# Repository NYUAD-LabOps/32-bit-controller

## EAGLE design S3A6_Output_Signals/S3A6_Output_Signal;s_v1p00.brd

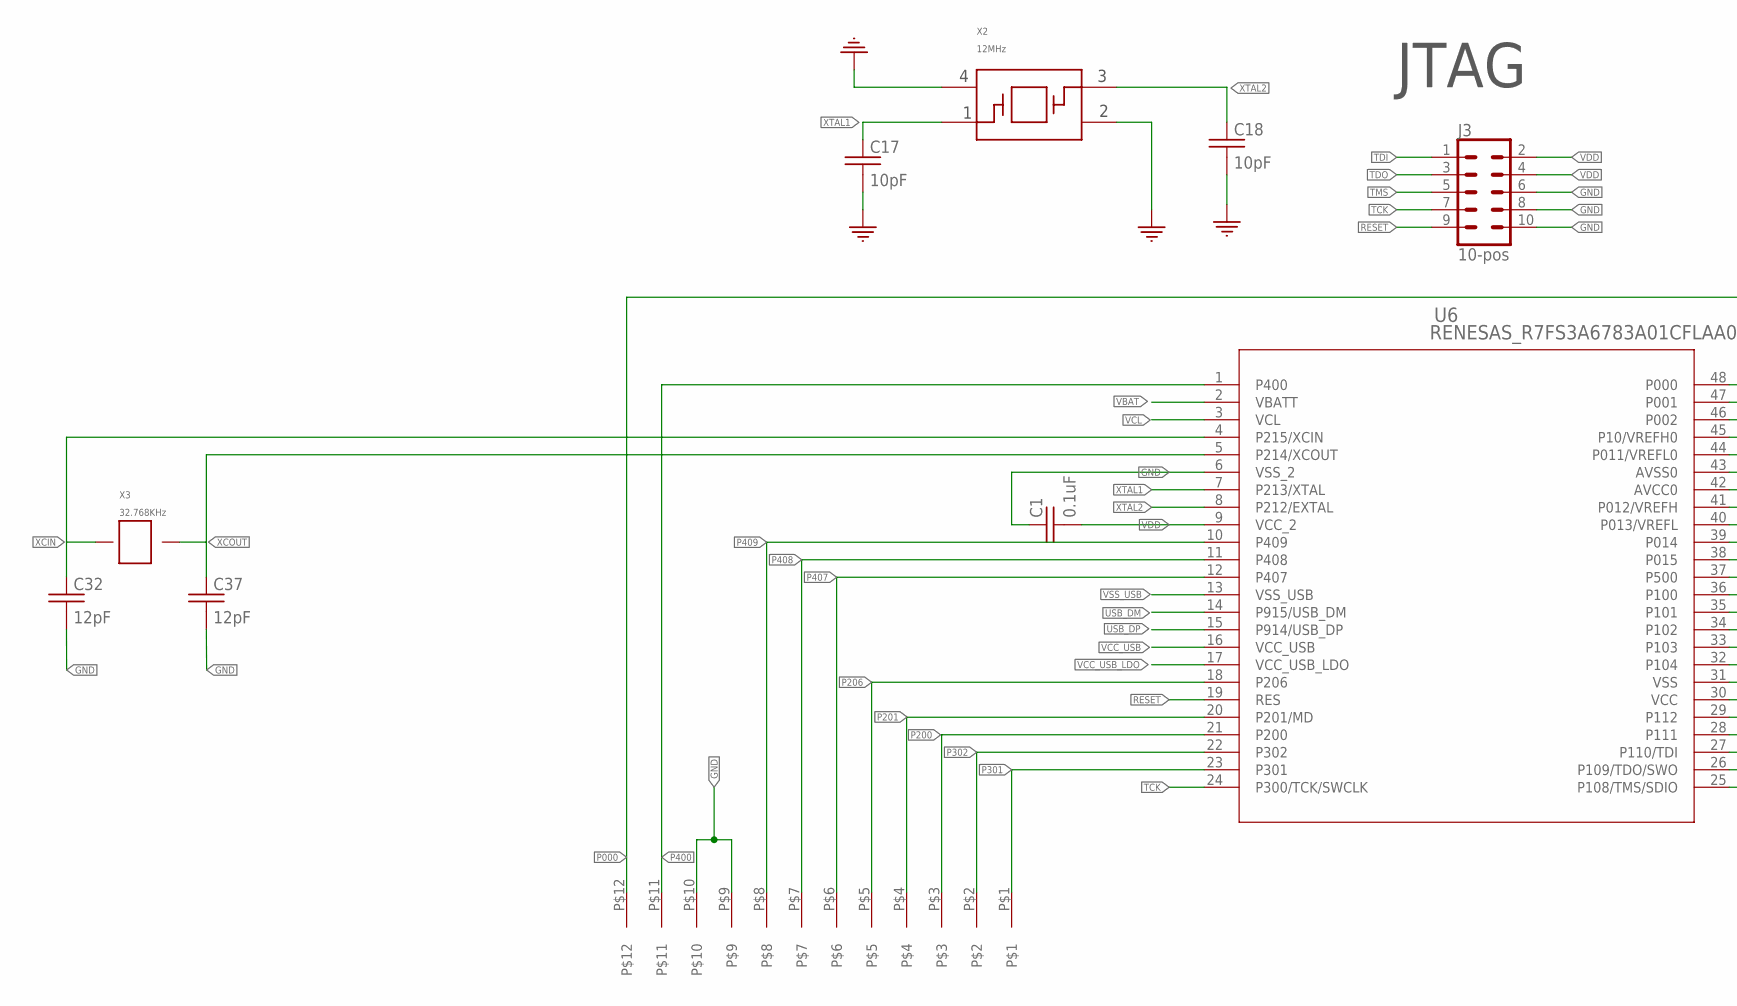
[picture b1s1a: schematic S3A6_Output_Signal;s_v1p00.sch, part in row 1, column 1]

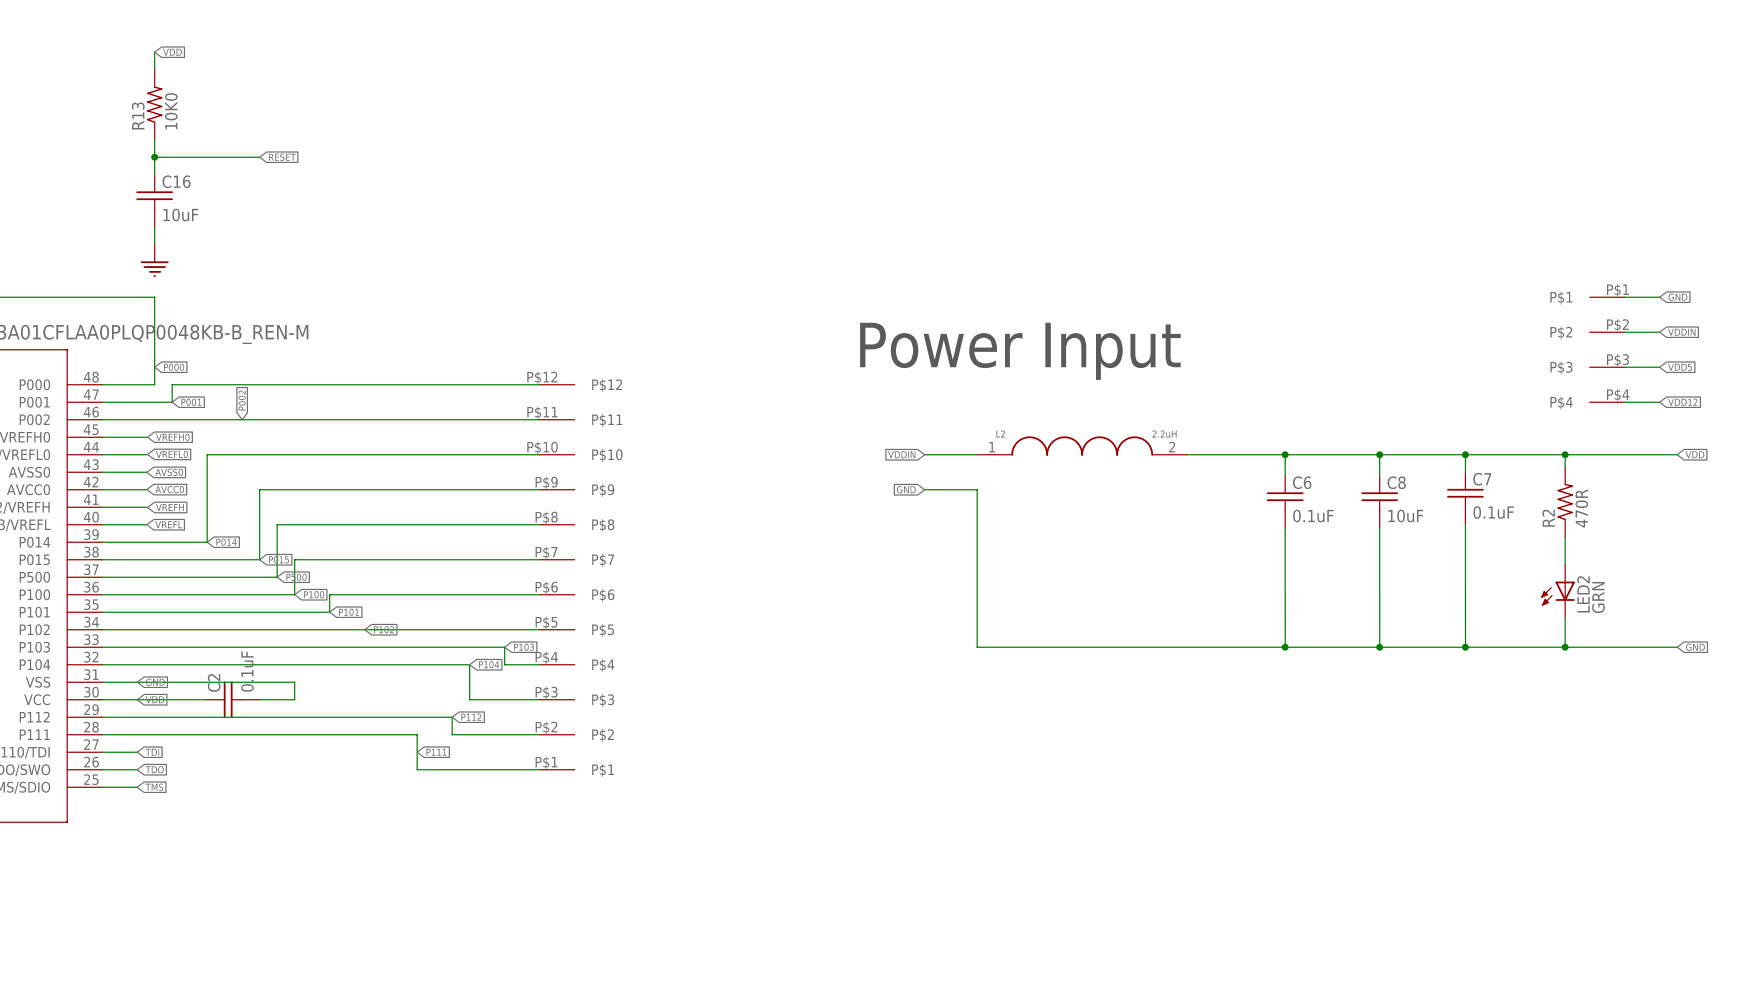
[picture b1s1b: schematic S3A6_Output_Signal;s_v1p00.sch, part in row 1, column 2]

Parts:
C1, C2, C6, C7: 0.1uF; 0402
C8, C16: 10uF; 0402
C17, C18: 10pF; 0402
C32, C37: 12pF; 0402
J3: 10-pos; 2X5
L2: 2.2uH; 1008_(2520_METRIC)
LED2: LED_0805_GREEN
PWR1: 4-pos; 1X4_3.81MM_PITCH
R2: 470R; 0402
R13: 10K0; 0402
U6: RENESAS_R7FS3A6783A01CFLAA0PLQP0048KB-B_REN-M; PLQP0048KB-B_REN-M
U$1, U$2: 1_X_12_HEADER_GENERIC_.1INCH; HEADER_1_X_12_.1_INCH
X2: 12MHz; SMD_3225
X3: 32.768KHz; SMD_X_2_PADS

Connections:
AVCC0: U6.42 (AVCC0)
AVSS0: U6.43 (AVSS0)
GND: C1.P$1 (1), C2.P$2 (2), C6.P$2 (2), C7.P$2 (2), C8.P$2 (2), C16.P$2 (2), C17.P$2 (2), C18.P$2 (2), C32.P$2 (2), C37.P$2 (2), J3.6, J3.8, J3.10, LED2.C, PWR1.P$1, U6.6 (VSS_2), U6.31 (VSS), U$1.P$9, U$1.P$10, X2.2, X2.4
unnamed: LED2.A, R2.P$1 (1)
P000: U6.48 (P000), U$1.P$12
P001: U6.47 (P001), U$2.P$12
P002: U6.46 (P002), U$2.P$11
P014: U6.39 (P014), U$2.P$10
P015: U6.38 (P015), U$2.P$9
P100: U6.36 (P100), U$2.P$7
P101: U6.35 (P101), U$2.P$6
P102: U6.34 (P102), U$2.P$5
P103: U6.33 (P103), U$2.P$4
P104: U6.32 (P104), U$2.P$3
P111: U6.28 (P111), U$2.P$1
P112: U6.29 (P112), U$2.P$2
P200: U6.21 (P200), U$1.P$3
P201: U6.20 (P201/MD), U$1.P$4
P206: U6.18 (P206), U$1.P$5
P301: U6.23 (P301), U$1.P$1
P302: U6.22 (P302), U$1.P$2
P400: U6.1 (P400), U$1.P$11
P407: U6.12 (P407), U$1.P$6
P408: U6.11 (P408), U$1.P$7
P409: U6.10 (P409), U$1.P$8
P500: U6.37 (P500), U$2.P$8
RESET: C16.P$1 (1), J3.9, R13.P$1 (1), U6.19 (RES)
TCK: J3.7, U6.24 (P300/TCK/SWCLK)
TDI: J3.1, U6.27 (P110/TDI)
TDO: J3.3, U6.26 (P109/TDO/SWO)
TMS: J3.5, U6.25 (P108/TMS/SDIO)
USB_DM: U6.14 (P915/USB_DM)
USB_DP: U6.15 (P914/USB_DP)
VBAT: U6.2 (VBATT)
VCC_USB: U6.16 (VCC_USB)
VCC_USB_LDO: U6.17 (VCC_USB_LDO)
VCL: U6.3 (VCL)
VDD: C1.P$2 (2), C2.P$1 (1), C6.P$1 (1), C7.P$1 (1), C8.P$1 (1), J3.2, J3.4, L2.2, R2.P$2 (2), R13.P$2 (2), U6.9 (VCC_2), U6.30 (VCC)
VDD5: PWR1.P$3
VDD12: PWR1.P$4
VDDIN: L2.1, PWR1.P$2
VREFH: U6.41 (P012/VREFH)
VREFH0: U6.45 (P10/VREFH0)
VREFL: U6.40 (P013/VREFL)
VREFL0: U6.44 (P011/VREFL0)
VSS_USB: U6.13 (VSS_USB)
XCIN: C32.P$1 (1), U6.4 (P215/XCIN), X3.P$1
XCOUT: C37.P$1 (1), U6.5 (P214/XCOUT), X3.P$2
XTAL1: C17.P$1 (1), U6.7 (P213/XTAL), X2.1
XTAL2: C18.P$1 (1), U6.8 (P212/EXTAL), X2.3

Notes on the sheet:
JTAG
Power Input

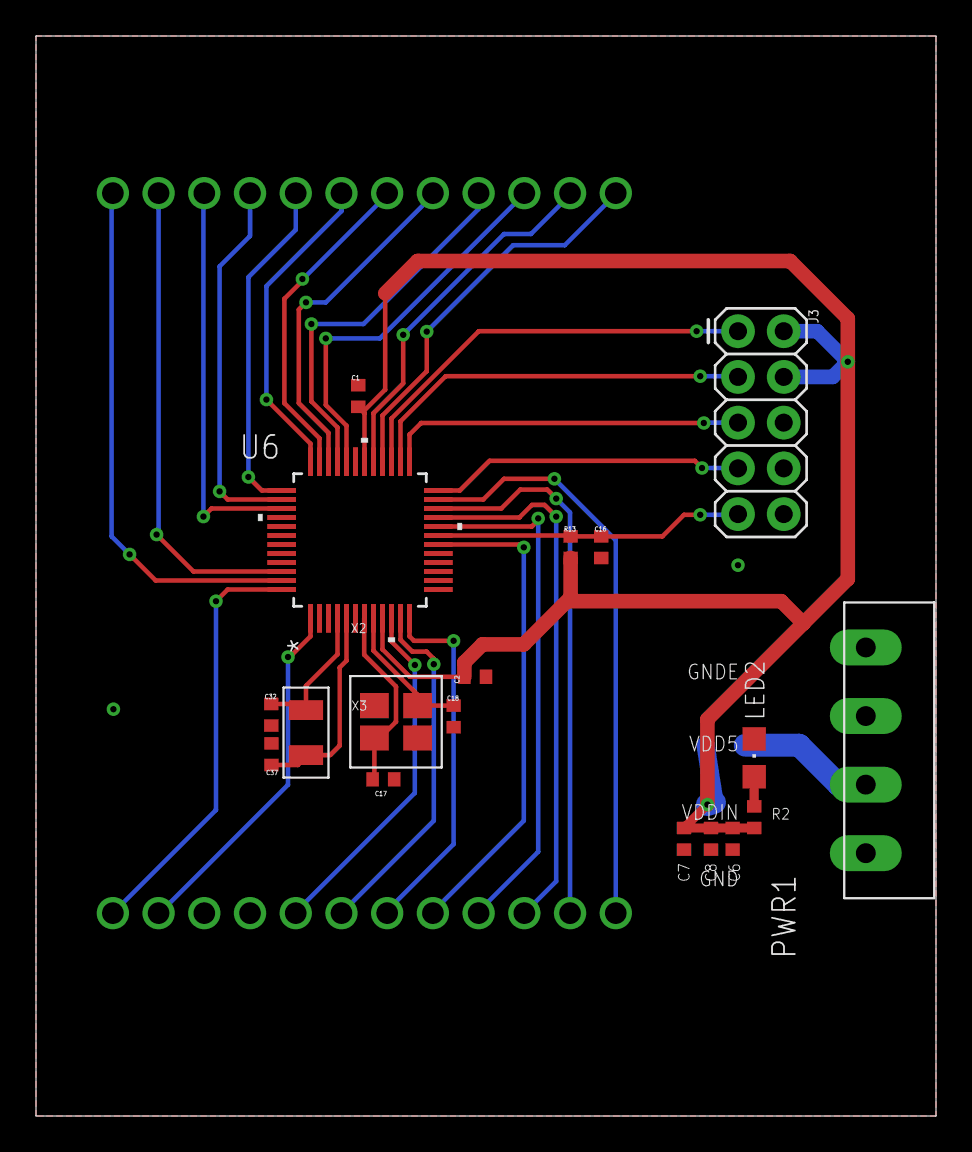
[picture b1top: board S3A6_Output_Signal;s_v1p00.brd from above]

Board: 2 copper layers, 50.0 x 60.0 mm, 21 parts (1 on the bottom side), 35 nets.

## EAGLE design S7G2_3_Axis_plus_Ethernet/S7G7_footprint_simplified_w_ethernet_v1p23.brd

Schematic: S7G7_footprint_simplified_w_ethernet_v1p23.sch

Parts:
C1, C8, C10, C11, C13, C14, C30, C31, C33, C34, C36, C37, C38, C39, C40, C44, C46, C49, C54, C55, C56, C58, C59, C60, C61: 0.1uF; 0402
C2, C16, C32: 1uF; 0402
C5, C35, C57: 10uF; 0402
C15: 100uF; C1210
C41, C42: 24pF; 0402
C43, C48: 22uF; 0603
C45: 2.2uF; 0402
C47: 100pF; 0402
C50, C51: 12pF; 0402
C52, C53: 18pF; 0402
FB2/2: FB_0805_120_OHM; 0805
J1, J11: CONN_05X2PTH; 2X5
J2: USB_MICRO-B
J3: USB_A; USB_A_SMT
J4: RJ45_WITH_ELEC; RJ45_TH_ELEC
J5, J6, J13, J14, J15: 3.81MM_1_X_4_RT_ANGLE_PLUG_HEADER; 1X4_3.81MM_PITCH
J7, J8, J12: CONN_05X2NO_SILK; 2X5_NOSILK
J9: SD_CARD_1140084168; AMPHENOL_1140084168
J10: HEADER_2_X_20_GENERIC; HEADER_2_X_20_.1_INCH
J16: CONN_05X2SHD_SMD; 2X5-SHROUDED_SMD
L3: 2.2uH; 1008_(2520_METRIC)
LED3: LED_0805_GREEN
R1, R12, R16, R17, R18, R26, R27: 10K0; 0402
R2, R3, R8, R9, R10, R11, R14, R20, R21: 1K; 0402
R4: 15K0; 0402
R5, R6: 27R0; 0402
R7: 30K0; 0402
R13, R23, R24: 470R0; 0402
R19: 2.2K; 0402
R25: 6k49; 0402
R28, R29: 1K50; 0402
R30, R31, R32, R33: 33R0; 0402
RXS2, RXS3, RXS4, RXS8: 1K; 0402
RYS3, RYS4, RYS5, RYS6, RYS7, RYS8, RYS15, RYS16: 1K; 0402
RZS2, RZS3, RZS4, RZS8: 1K; 0402
U2: AP2141DWG-5; SOT-23-5
U3: KSZ8081RNACAQFN-24-M; QFN-24-M
U4: S7G2LQFP176; LQFP176_24X24
U7, U8, U9, U10, U12, U13, U14, U15, U16, U17, U18, U19, U32, U33, U34, U35: BC846BW; SOT323
U$1, U$5, U$6, U$8, U$10, U$12, U$13, U$14, U$15, U$16, U$17, U$18, U$32, U$33, U$34, U$35: 1K; 0402
U$3: XTAL_25_MHZ; SMD_3225
U$4: 10uF; 0402
X3: 32.768KHZ; SMD_X_2_PADS
X4: 24MHZ; SMD_3225

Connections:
C58: C39.P$1 (1), J4.4 (CT1)
C60: C40.P$1 (1), J4.5 (CT2)
CRS_DV: R33.P$2 (2), U3.15 (CRS_DV/PHYAD[1:0])
D+: J2.P$3 (D+), R6.P$2 (2)
D-: J2.P$2 (D-), R5.P$2 (2)
ETH: U3.16 (REF_CLK), U4.9 (P7_1)
ETH_CRS_DV: R33.P$1 (1), U4.13 (P7_5)
ETH_IRQ14: R26.P$1 (1), U3.18 (INTRP), U4.159 (P0_10/AN103)
ETH_MDC: R28.P$1 (1), U3.11 (MDC), U4.4 (P4_3)
ETH_MDIO: R29.P$1 (1), U3.10 (MDIO), U4.5 (P4_4)
ETH_RESET: R27.P$1 (1), U3.24 (!RST), U4.172 (P8_6), U$4.P$1 (1)
ETH_RXD0: R31.P$1 (1), U4.10 (P7_2)
ETH_RXD1: R30.P$1 (1), U4.11 (P7_3)
ETH_RX_ER: R32.P$1 (1), U4.12 (P7_4)
ETH_TXD0: U3.20 (TXD0), U4.8 (P7_0)
ETH_TXD1: U3.21 (TXD1), U4.7 (P4_6)
ETH_TXD_EN: U3.19 (TXEN), U4.6 (P4_5)
F0_OUT: J5.P$1, J6.P$1, J13.P$1, J14.P$1, U8.3 (C(3)), U13.3 (C(3)), U17.3 (C(3)), U33.3 (C(3))
F1_OUT: J5.P$2, J6.P$2, J13.P$2, J14.P$2, U9.3 (C(3)), U14.3 (C(3)), U18.3 (C(3)), U34.3 (C(3))
F2_OUT: J5.P$3, J6.P$3, J13.P$3, J14.P$3, U7.3 (C(3)), U12.3 (C(3)), U16.3 (C(3)), U32.3 (C(3))
F3_OUT: J5.P$4, J6.P$4, J13.P$4, J14.P$4, U10.3 (C(3)), U15.3 (C(3)), U19.3 (C(3)), U35.3 (C(3))
GND: C1.P$1 (1), C2.P$1 (1), C5.P$2 (2), C8.P$2 (2), C10.P$1 (1), C11.P$2 (2), C13.P$1 (1), C14.P$1 (1), C15.2, C16.P$2 (2), C30.P$1 (1), C31.P$2 (2), C32.P$2 (2), C33.P$2 (2), C34.P$2 (2), C35.P$2 (2), C36.P$1 (1), C37.P$1 (1), C38.P$2 (2), C39.P$2 (2), C40.P$2 (2), C41.P$2 (2), C42.P$2 (2), C43.2, C44.P$2 (2), C45.P$2 (2), C46.P$2 (2), C47.P$2 (2), C48.2, C49.P$2 (2), C50.P$2 (2), C51.P$2 (2), C52.P$2 (2), C53.P$2 (2), C54.P$1 (1), C55.P$1 (1), C56.P$1 (1), C57.P$2 (2), C58.P$2 (2), C59.P$2 (2), C60.P$2 (2), C61.P$1 (1), J1.1, J1.2, J2.P$5 (GND), J3.GND, J4.8, J4.10 (GLO), J9.6 (SUPPLY_VOLTAGE_GROUND), J11.6, J11.8, J11.10, J16.2, J16.4, J16.6, J16.8, J16.10, LED3.C, R7.P$1 (1), R16.P$1 (1), R17.P$1 (1), R19.P$1 (1), R25.P$1 (1), U2.2 (GND), U3.22 (GND), U3.25, U4.22 (VSS1), U4.28 (AVSS_USBHS), U4.29 (PVSS_USBHS), U4.30 (VSS2_USBHS), U4.33 (VSS1_USBHS), U4.35 (VSSIO), U4.45 (VSS_USB), U4.60 (VSS(IO)2), U4.63 (VSS(IO/DCDC)), U4.66 (VCC_DCDC(IO/DCDC)), U4.83 (VSS(IO)3), U4.98 (VSS(IO)4), U4.111 (VSS(IO)5), U4.124 (VSS(IO)6), U4.139 (VSS(IO)7), U4.150 (VSS(IO)8), U4.153 (VREFL), U4.156 (AVSS0), U4.157 (VREFL0), U4.170 (VSS(IO)9), U7.2 (E(1)), U8.2 (E(1)), U9.2 (E(1)), U10.2 (E(1)), U12.2 (E(1)), U13.2 (E(1)), U14.2 (E(1)), U15.2 (E(1)), U16.2 (E(1)), U17.2 (E(1)), U18.2 (E(1)), U19.2 (E(1)), U32.2 (E(1)), U33.2 (E(1)), U34.2 (E(1)), U35.2 (E(1)), U$1.P$2 (2), U$3.2, U$3.4, U$4.P$2 (2), U$5.P$2 (2), U$6.P$2 (2), U$8.P$2 (2), U$10.P$2 (2), U$12.P$2 (2), U$13.P$2 (2), U$14.P$2 (2), U$15.P$2 (2), U$16.P$2 (2), U$17.P$2 (2), U$18.P$2 (2), U$32.P$2 (2), U$33.P$2 (2), U$34.P$2 (2), U$35.P$2 (2), X4.2, X4.4
GNDE: J1.9, J1.10, J2.P$6 (SHIELD1), J2.P$7 (SHIELD2), J2.P$8 (SHIELD3), J2.P$9 (SHIELD4), J3.SHLD1 (SHIELD_1), J3.SHLD2 (SHIELD_2), J4.13 (GNDE0), J4.14 (GNDE1), J9.S1 (SHIELD), J9.S2 (SHIELD), J9.S3 (SHIELD), J9.S4 (SHIELD)
GP4: U4.49 (P2_7)
ID: J2.P$4 (ID)
IIC_0_SCL: J7.10, R11.P$2 (2), U4.1 (P4_0)
IIC_0_SDA: J7.9, R14.P$2 (2), U4.2 (P4_1)
IIC_1_SCL: J10.P$5, R20.P$2 (2), U4.132 (P1_0)
IIC_1_SDA: J10.P$6, R21.P$2 (2), U4.131 (P1_1)
INT_AI_LS_0: J15.P$1, U4.3 (P4_2)
INT_AI_LS_1: J15.P$2, U4.43 (P4_8)
INT_AI_LS_2: J15.P$3, U4.53 (P2_3)
INT_AI_LS_3: J15.P$4, U4.54 (P2_2)
INT_MI_01: J10.P$39, U4.87 (P3_1)
INT_MI_02: J10.P$40, U4.86 (P3_2)
INT_MI_03: J10.P$9, U4.128 (P1_4)
INT_MI_04: J10.P$10, U4.127 (P1_5)
INT_MI_05: J10.P$1
LED1/SPEED: J4.11 (YLO), U3.23 (LED0/ANEN_SPEED)
M0_DIR: RXS4.P$1 (1), U4.39 (P4_12)
M0_STEP: RXS2.P$1 (1), U4.16 (PB_0)
M1_DIR: RYS7.P$1 (1), U4.40 (P4_11)
M1_STEP: RYS3.P$1 (1), U4.36 (P4_15)
M2_DIR: RZS4.P$1 (1), U4.41 (P4_10)
M2_STEP: RZS2.P$1 (1), U4.37 (P4_14)
M3_DIR: RYS8.P$1 (1), U4.42 (P4_9)
M3_STEP: RYS4.P$1 (1), U4.38 (P4_13)
unnamed: C37.P$2 (2), U4.148 (VCL2)
unnamed: LED3.A, R13.P$1 (1)
unnamed: C38.P$1 (1), U4.19 (VCLO)
unnamed: C31.P$1 (1), U4.62 (VCL1)
unnamed: R17.P$2 (2), U4.64 (VLO1(DCDC))
unnamed: R16.P$2 (2), U4.65 (VLO2(DCDC))
unnamed: R19.P$2 (2), U4.27 (USBHS_RREF)
unnamed: RZS2.P$2 (2), U7.1 (B(2)), U$1.P$1 (1)
unnamed: RXS2.P$2 (2), U8.1 (B(2)), U$5.P$1 (1)
unnamed: RYS3.P$2 (2), U9.1 (B(2)), U$6.P$1 (1)
unnamed: RYS4.P$2 (2), U10.1 (B(2)), U$8.P$1 (1)
unnamed: RZS3.P$2 (2), U12.1 (B(2)), U$10.P$1 (1)
unnamed: RXS3.P$2 (2), U13.1 (B(2)), U$12.P$1 (1)
unnamed: RYS5.P$2 (2), U14.1 (B(2)), U$13.P$1 (1)
unnamed: RYS6.P$2 (2), U15.1 (B(2)), U$14.P$1 (1)
unnamed: RZS4.P$2 (2), U16.1 (B(2)), U$15.P$1 (1)
unnamed: RXS4.P$2 (2), U17.1 (B(2)), U$16.P$1 (1)
unnamed: RYS7.P$2 (2), U18.1 (B(2)), U$17.P$1 (1)
unnamed: RYS8.P$2 (2), U19.1 (B(2)), U$18.P$1 (1)
unnamed: RZS8.P$2 (2), U32.1 (B(2)), U$32.P$1 (1)
unnamed: RXS8.P$2 (2), U33.1 (B(2)), U$33.P$1 (1)
unnamed: RYS15.P$2 (2), U34.1 (B(2)), U$34.P$1 (1)
unnamed: RYS16.P$2 (2), U35.1 (B(2)), U$35.P$1 (1)
NC: J4.7
P0_00: J7.3, U4.169 (P0_0/AN0\00)
P0_01: J7.4, U4.168 (P0_1/AN001)
P0_02: J7.1, U4.167 (P0_2/AN002)
P0_03: J7.2, U4.166 (P0_3/PGAVSS000)
P0_04: J8.9, U4.165 (P0_4/AN100)
P0_05: J8.10, U4.164 (P0_5/AN101)
P0_06: J8.7, U4.163 (P0_6/AN102)
P0_07: J8.8, U4.162 (P0_7/PGVSS100)
P0_08: J8.5, U4.161 (P0_8/AN003)
P0_09: J8.6, U4.160 (P0_9/AN004)
P0_14: J8.3, U4.152 (P0_14/DA0/AN005/AN105)
P0_15: J8.4, U4.151 (P0_15/DA1/AN006/AN106)
P1_02: J10.P$7, U4.130 (P1_2)
P1_03: J10.P$8, U4.129 (P1_3)
P1_06: J10.P$11, U4.126 (P1_6)
P1_07: J10.P$12, U4.125 (P1_7)
P1_11: J10.P$38, U4.92 (P1_11)
P1_12: J10.P$37, U4.93 (P1_12)
P1_13: J10.P$36, U4.94 (P1_13)
P1_14: J10.P$35, U4.95 (P1_14)
P1_15: J10.P$34, U4.96 (P1_15)
P2_00: J16.3, R3.P$2 (2), U4.69 (P2_0(INPUT_ONLY))
P2_01: J16.1, R2.P$2 (2), U4.68 (P2_1/MD)
P3_03: J12.1, U4.85 (P3_3)
P3_04: J12.2, U4.82 (P3_4)
P3_05: J12.3, U4.81 (P3_5)
P3_06: J12.4, U4.80 (P3_6)
P3_07: J12.5, U4.79 (P3_7)
P3_09: J12.6, U4.77 (P3_9)
P3_10: J12.7, U4.76 (P3_10)
P3_11: J12.8, U4.75 (P3_11)
P3_12: J12.9, U4.74 (P3_12)
P5_11: J7.7, U4.176 (P5_11)
P5_12: J7.8, U4.175 (P5_12)
P5_13: J7.5, U4.174 (P5_13)
P6_00: J10.P$13, U4.122 (P6_0)
P6_01: J10.P$14, U4.121 (P6_1)
P6_02: J10.P$15, U4.120 (P6_2)
P6_03: J10.P$16, U4.119 (P6_3)
P6_04: J10.P$17, U4.118 (P6_4)
P6_05: J10.P$18, U4.117 (P6_5)
P6_06: J10.P$19, U4.116 (P6_6)
P6_07: J10.P$20, U4.115 (P6_7)
P6_08: J10.P$33, U4.99 (P6_8)
P6_09: J10.P$32, U4.100 (P6_9)
P6_10: J10.P$31, U4.101 (P6_10)
P6_11: J10.P$30, U4.102 (P6_11)
P6_12: J10.P$29, U4.103 (P6_12)
P6_13: J10.P$28, U4.104 (P6_13)
P6_14: J10.P$27, U4.105 (P6_14)
P6_15: J10.P$26, U4.106 (P6_15)
P7_06: U4.14 (P7_6)
P7_07: U4.15 (P7_7)
P8_00: J10.P$4, U4.133 (P8_0)
P8_01: J10.P$3, U4.134 (P8_1)
P8_02: J10.P$2, U4.135 (P8_2)
P8_03: J8.2, U4.136 (P8_3)
P8_04: J8.1, U4.137 (P8_4)
P8_05: J7.6, U4.173 (P8_5)
P9_05: J12.10, U4.73 (P9_5)
P9_06: J16.9, R10.P$2 (2), U4.72 (P9_6)
P9_07: J16.7, R9.P$2 (2), U4.71 (P9_7)
P9_08: J16.5, R8.P$2 (2), U4.70 (P9_8)
PA_00: J10.P$21, U4.114 (PA_0)
PA_01: J10.P$22, U4.113 (PA_1)
PA_08: J10.P$25, U4.107 (PA_8)
PA_09: J10.P$24, U4.108 (PA_9)
PA_10: J10.P$23, U4.109 (PA_10)
R51: J4.12 (YHI), R23.P$1 (1)
R52: J4.9 (GHI), R24.P$1 (1)
RELAY_0: RYS6.P$1 (1), U4.59 (P9_1)
RELAY_1: RZS3.P$1 (1), U4.58 (P9_0)
RELAY_2: RYS5.P$1 (1), U4.57 (P3_15)
RELAY_3: RXS3.P$1 (1), U4.56 (P3_14)
RELAY_4: RYS16.P$1 (1), U4.55 (P3_13)
RELAY_5: RZS8.P$1 (1), U4.52 (P2_4)
RELAY_6: RYS15.P$1 (1), U4.51 (P2_5)
RELAY_7: RXS8.P$1 (1), U4.50 (P2_6)
RESET: C57.P$1 (1), J11.9, R18.P$1 (1), U4.67 (RES#)
REXT: C47.P$1 (1), R25.P$2 (2), U3.9 (REXT)
RXD0: R31.P$2 (2), U3.13 (RXD0)
RXD1: R30.P$2 (2), U3.12 (RXD1)
RXER: R32.P$2 (2), U3.17 (RXER)
RXM: J4.6 (RD-), U3.3 (RXM)
RXP: J4.3 (RD+), U3.4 (RXP)
SD1_CD: J9.10 (CD_SWITCH2), U4.146 (P5_6/AN019)
SD1_CLK: J9.5 (CLOCK), U4.140 (P5_0/AN016)
SD1_CMD: J9.3 (COMMAND/RESPONSE), U4.141 (P5_1/AN116)
SD1_DAT0: J9.7 (DATA_LINE[BIT_0]), U4.142 (P5_2/AN017)
SD1_DAT1: J9.8 (DATA_LINE[BIT_1]), U4.143 (P5_3/AN117)
SD1_DAT2: J9.1 (DATA_LINE[BIT_2]), U4.144 (P5_4/AN018)
SD1_DAT3: J9.2 (CARD_DETECT/DATA_LINE[BIT_3]), U4.145 (P5_5/AN118)
SD1_WP: J9.9 (CD_SWITCH1), U4.147 (P5_7/AN119)
TCK: J11.7, U4.88 (P3_0)
TDI: J11.1, U4.91 (P1_10)
TDO: J11.3, U4.90 (P1_9)
TMS: J11.5, U4.89 (P1_8)
TXM: J4.2 (TD-), U3.5 (TXM)
TXP: J4.1 (TD+), U3.6 (TXP)
USBHS_FAULT: R12.P$1 (1), U2.3 (FLG), U4.78 (P3_8)
USBHS_N: J3.D-, U4.31 (USBHS_DM)
USBHS_P: J3.D+, U4.32 (USBHS_DP)
USBHS_VBUS: C11.P$1 (1), C15.1, J3.VBUS, U2.5 (OUT), U4.17 (PB_1)
USBHS_VBUSEN: R1.P$1 (1), U2.1 (EN)
USB_N: R5.P$1 (1), U4.46 (USB_DM)
USB_P: R6.P$1 (1), U4.47 (USB_DP)
USB_VBUS_B: R4.P$1 (1), U4.44 (P4_7)
VBUS: C16.P$1 (1), J2.P$1 (VBUS), R4.P$2 (2), R7.P$2 (2)
VCL_F(FLASH): C36.P$2 (2), U4.112 (VCL_F(FLASH))
VDD: C1.P$2 (2), C2.P$2 (2), C10.P$2 (2), C13.P$2 (2), C14.P$2 (2), C30.P$2 (2), C32.P$1 (1), C33.P$1 (1), C34.P$1 (1), C35.P$1 (1), C48.1, C49.P$1 (1), C54.P$2 (2), C55.P$2 (2), C56.P$2 (2), C58.P$1 (1), C59.P$1 (1), C60.P$1 (1), C61.P$2 (2), FB2/2.1, J9.4 (SUPPLY_VOLTAGE), J11.2, J11.4, L3.2, R2.P$1 (1), R3.P$1 (1), R8.P$1 (1), R9.P$1 (1), R10.P$1 (1), R11.P$1 (1), R13.P$2 (2), R14.P$1 (1), R18.P$2 (2), R20.P$1 (1), R21.P$1 (1), R23.P$2 (2), R24.P$2 (2), R26.P$2 (2), R27.P$2 (2), R28.P$2 (2), R29.P$2 (2), U3.14 (VDDIO), U4.25 (VCC1), U4.26 (AVCC_SUBHS), U4.34 (VCC_USBHS), U4.48 (VCC_USB), U4.61 (VCC(IO)2), U4.84 (VCC(IO)3), U4.97 (VCC(IO)4), U4.110 (VCC(IO)5), U4.123 (VCC(IO)6), U4.138 (VCC(IO)7), U4.149 (VCC(IO)8), U4.154 (VREFH), U4.155 (AVCC0), U4.158 (VREFH0), U4.171 (VCC(IO)9)
VDD5: C5.P$1 (1), C8.P$1 (1), J1.5, J1.6, R1.P$2 (2), R12.P$2 (2), U2.4 (VIN)
VDD12: J1.7, J1.8
VDDIN: J1.3, J1.4, L3.1
VDD_1.2: C45.P$1 (1), C46.P$1 (1), U3.1 (VDD_1.2)
VDD_ENET1: C43.1, C44.P$1 (1), FB2/2.2, U3.2 (VDDA_3.3)
XCIN: C50.P$1 (1), U4.20 (XCIN), X3.P$1
XCOUT: C51.P$1 (1), U4.21 (XCOUT), X3.P$2
XII: C42.P$1 (1), U3.8 (XI), U$3.1
XOO: C41.P$1 (1), U3.7 (XO), U$3.3
XTAL1: C52.P$1 (1), U4.23 (P2_13/XTAL), X4.1
XTAL2: C53.P$1 (1), U4.24 (P2_12/EXTAL), X4.3

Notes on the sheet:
Power Input
JTAG

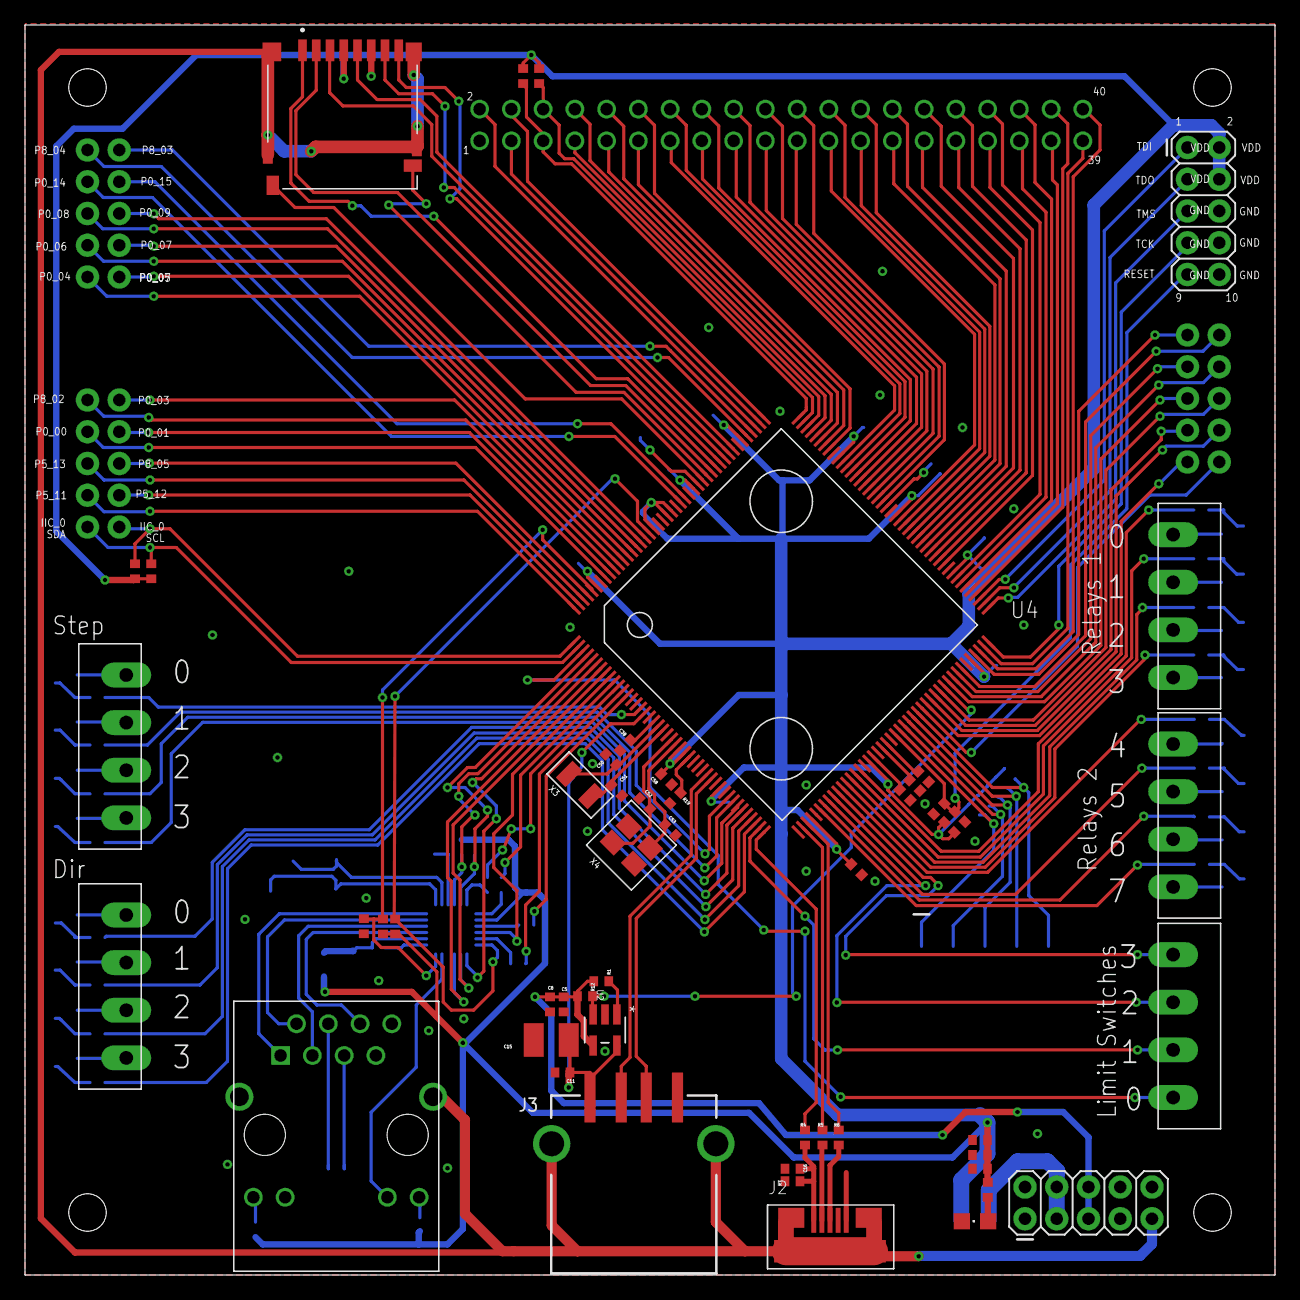
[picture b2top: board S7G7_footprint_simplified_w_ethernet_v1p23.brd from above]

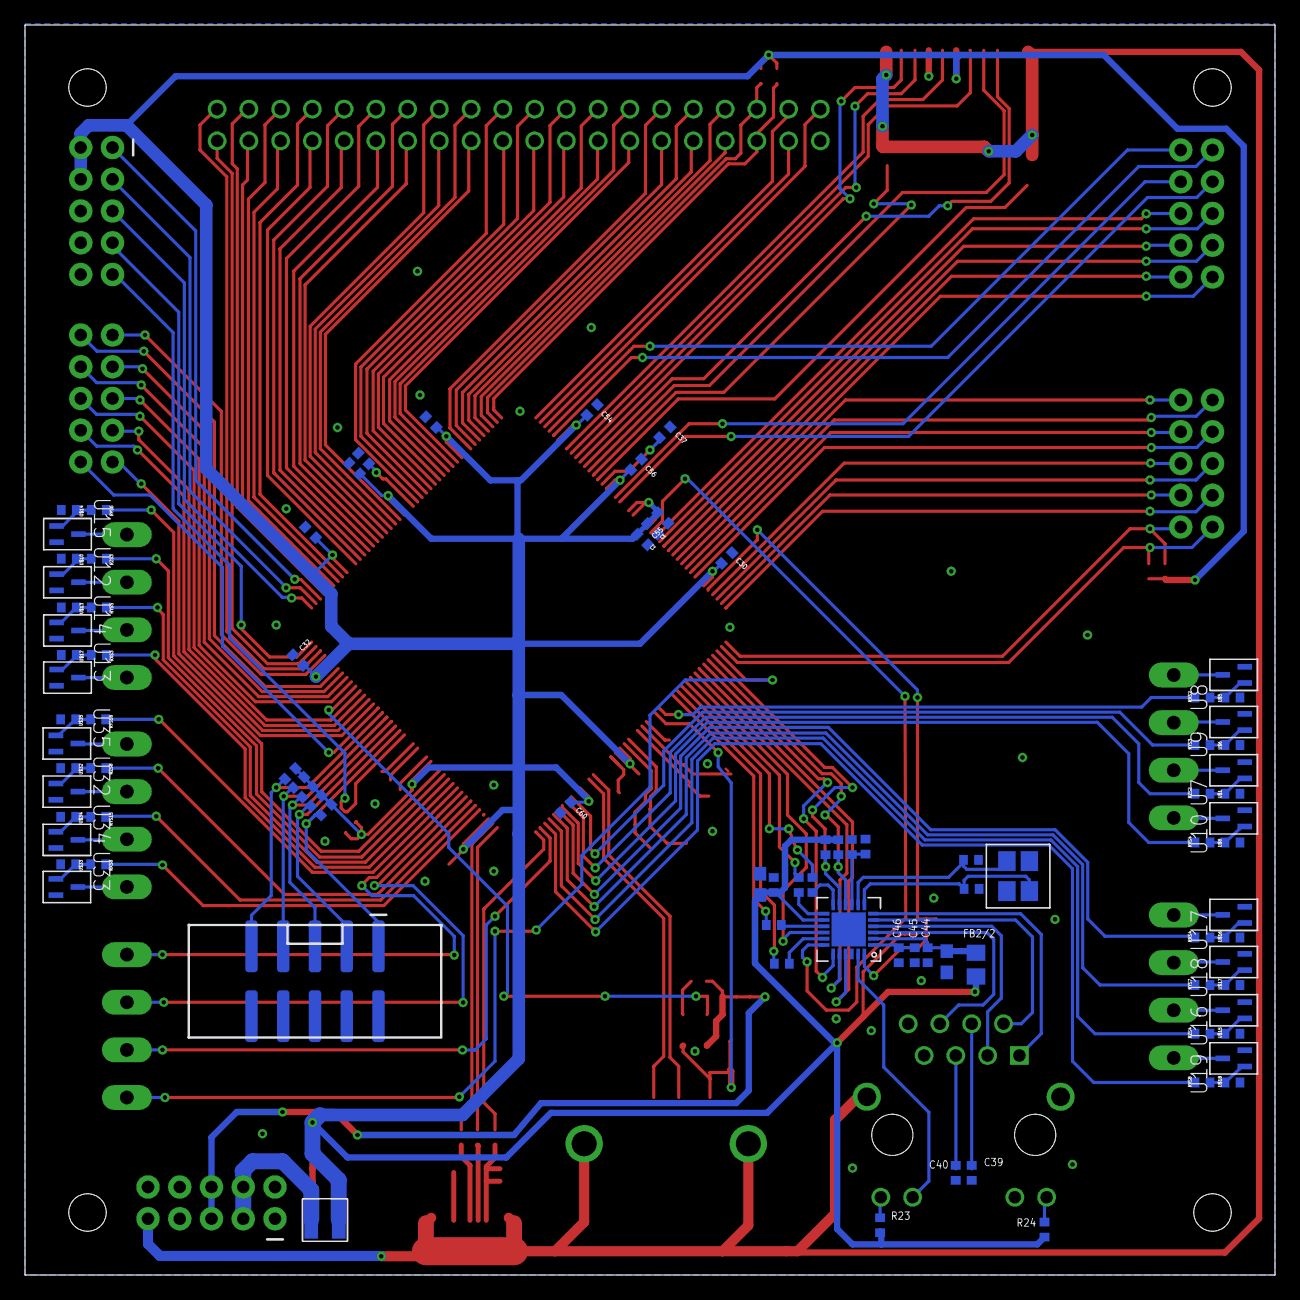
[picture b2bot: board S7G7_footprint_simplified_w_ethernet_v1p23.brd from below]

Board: 2 copper layers, 100.0 x 100.0 mm, 147 parts (91 on the bottom side), 186 nets.

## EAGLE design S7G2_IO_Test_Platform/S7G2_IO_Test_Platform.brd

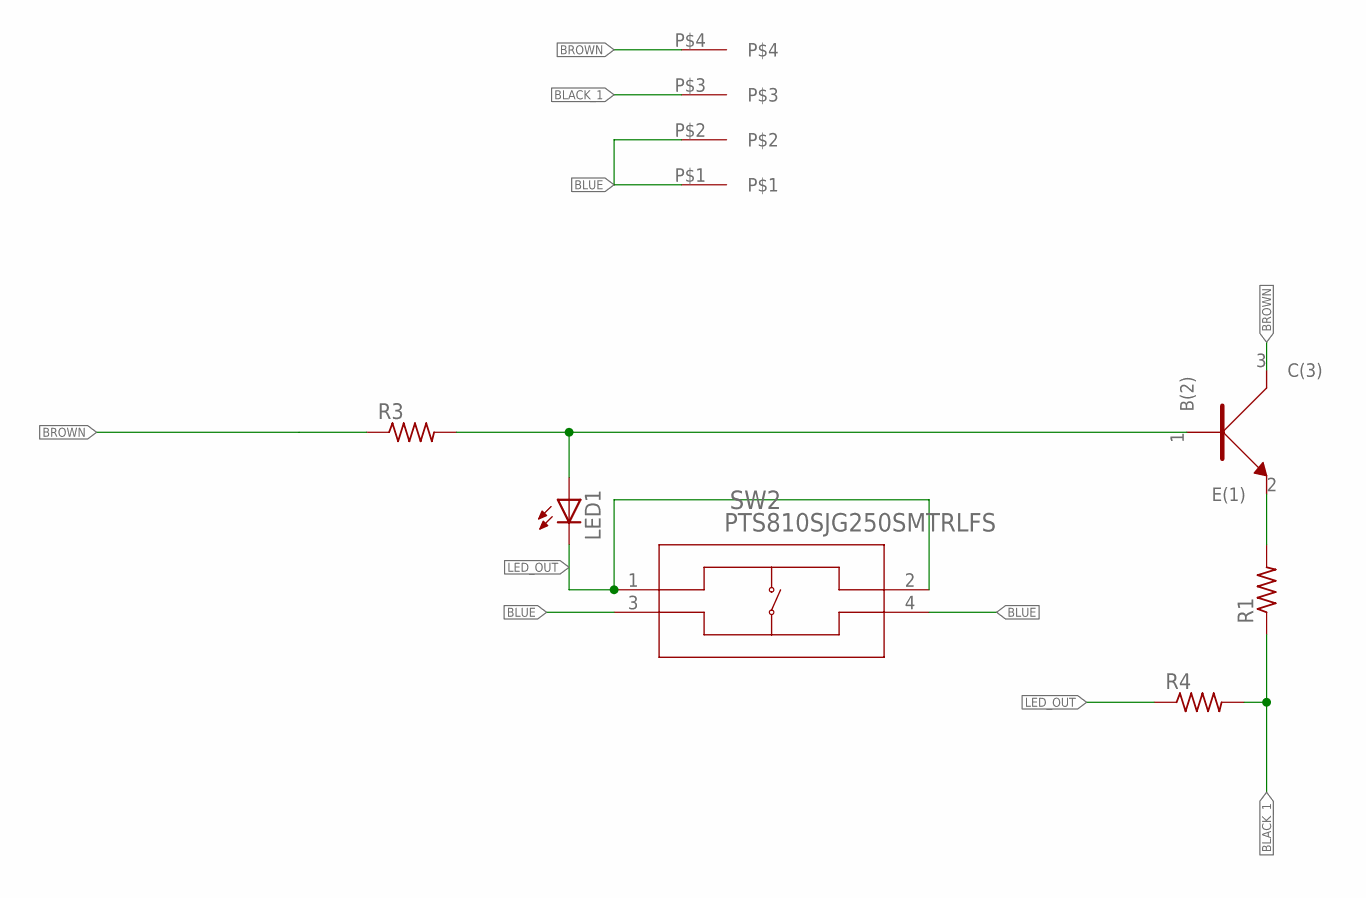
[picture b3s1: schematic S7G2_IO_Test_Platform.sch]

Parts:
J8: 4-pos; 1X4_3.81MM_PITCH
LED1: Green; 0805
R1, R3, R4: R_0805; 0805
SW2: PTS810SJG250SMTRLFS; PTS810
U1: NPN; SOT323

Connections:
BLACK_1: J8.P$3, R1.1, R4.2
BLUE: J8.P$1, J8.P$2, SW2.3, SW2.4
BROWN: J8.P$4, R3.1, U1.3 (C(3))
LED_OUT: LED1.2 (C), R4.1, SW2.1, SW2.2
unnamed: LED1.1 (A), R3.2, U1.1 (B(2))
unnamed: R1.2, U1.2 (E(1))

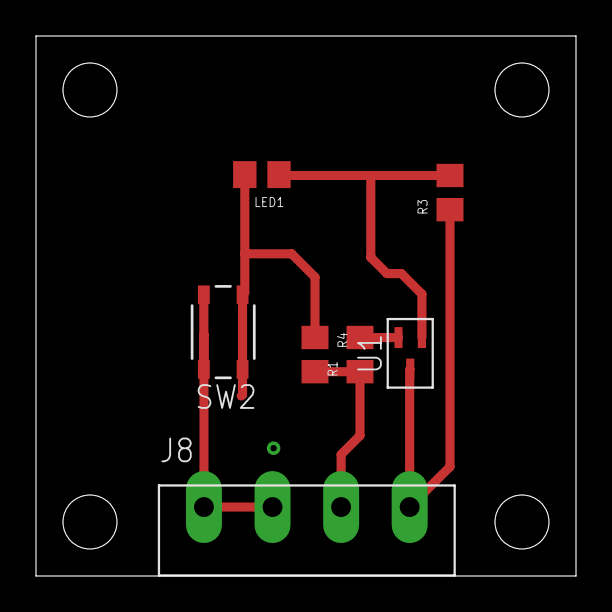
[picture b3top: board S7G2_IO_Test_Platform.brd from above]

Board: 2 copper layers, 30.0 x 30.0 mm, 7 parts (0 on the bottom side), 6 nets.

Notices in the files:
parts and their libraries:
COPYRIGHT: Copyright (C) 2021 Accelerated Designs. All rights reserved
COPYRIGHT: Copyright (C) 2018 Accelerated Designs. All rights reserved
